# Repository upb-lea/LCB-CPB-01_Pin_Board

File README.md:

# Pin board LCB-CPB-01 for the LEA control board

This is the pin board extension board for the LEA control board LCB-CCB-01. Please refer to the [LCB-CCB-01 repository](https://github.com/upb-lea/LCB-CCB-01_LEA_Control_Board) for a PCB and project overview.

Note, that you also need to install the `LEA KiCad Library` to view this PCB in this repository. To do this, follow the instructions mentioned [here](https://github.com/upb-lea/LCB-CCB-01_LEA_Control_Board/blob/main/README.md#downloading-this-project-and-folder-structure).

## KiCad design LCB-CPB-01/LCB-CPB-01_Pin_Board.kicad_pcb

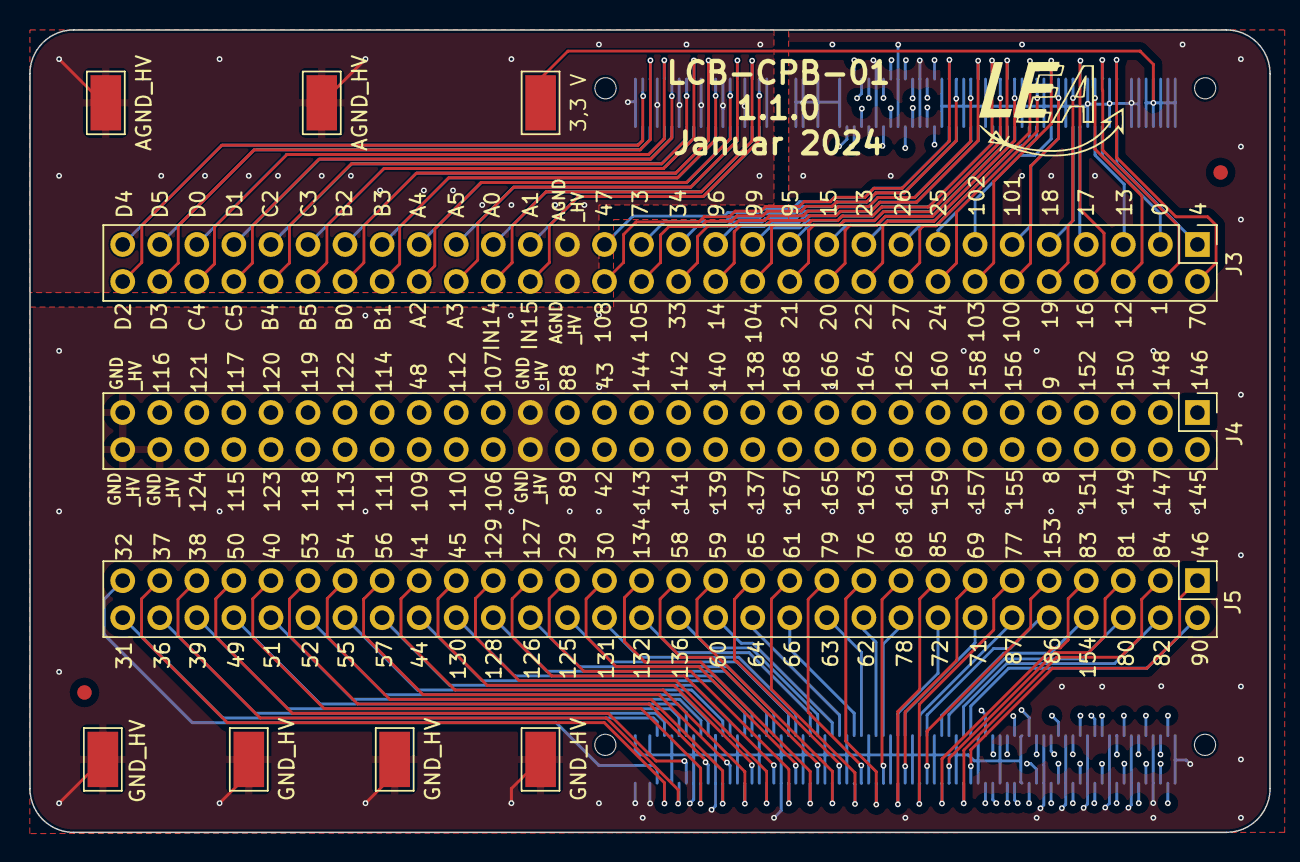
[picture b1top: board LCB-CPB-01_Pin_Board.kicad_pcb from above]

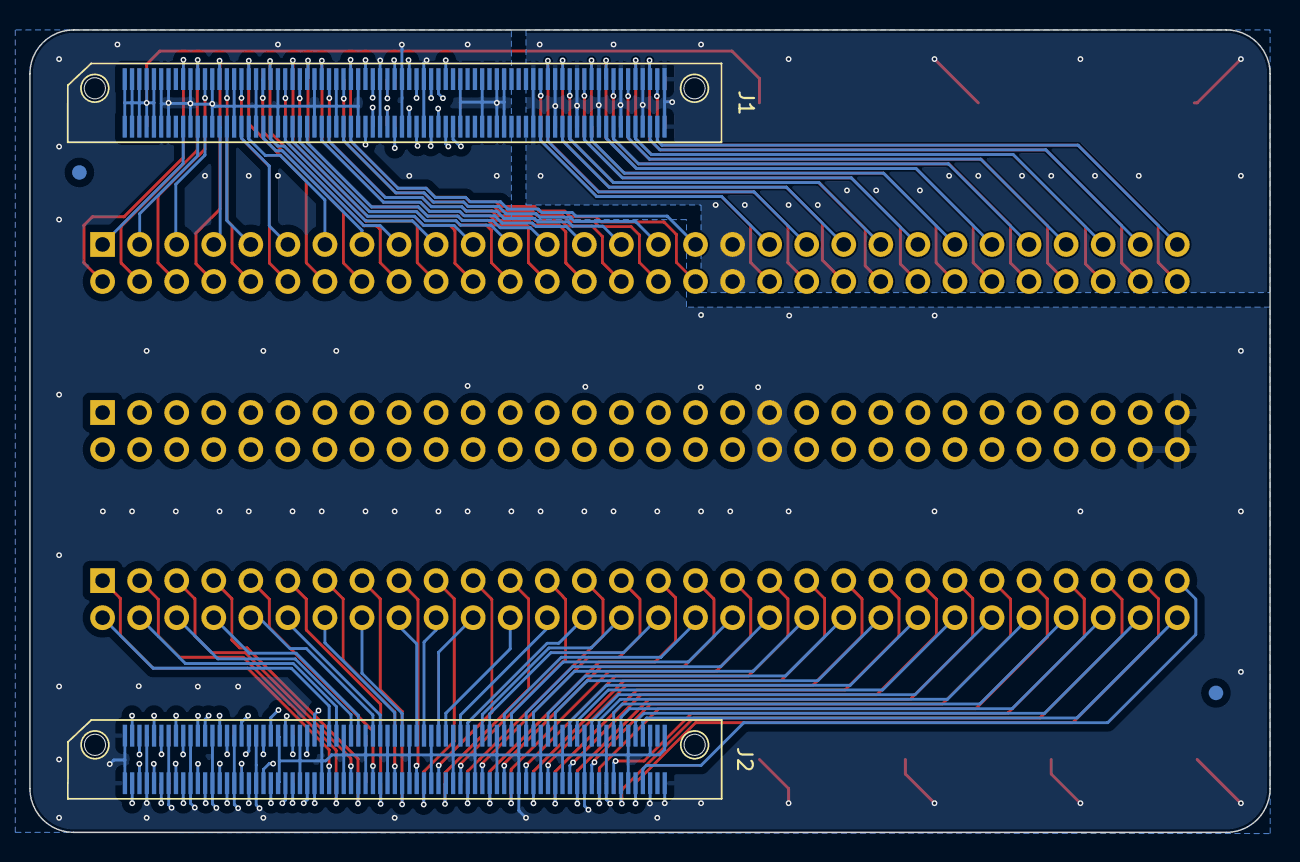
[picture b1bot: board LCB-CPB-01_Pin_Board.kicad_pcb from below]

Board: 4 copper layers, 85.0 x 55.0 mm, 17 parts (4 on the bottom side), 176 nets.

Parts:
3,3 V: TP_Keystone_Electronics_5019; TestPoint_KeystoneElectronics5019
AGND_HV: TP_Keystone_Electronics_5019; TestPoint_KeystoneElectronics5019
AGND_HV#2: TP_Keystone_Electronics_5019; TestPoint_KeystoneElectronics5019
GND_HV: TP_Keystone_Electronics_5019; TestPoint_KeystoneElectronics5019
GND_HV#2, GND_HV#3: TP_Keystone_Electronics_5019; TestPoint_KeystoneElectronics5019
J1, J2: ERM5-075-05.0-L-DV-K-TR; ERM5-075-05.0-L-DV
J3, J4, J5: 02x30_Row_Letter_Last; PinHeader_2x30_P2.54mm_Vertical
O1: SYM_LEA_Logo; SYM_lea_logo
O2, O3, O4, O5: Fiducial_medium; Fiducials_medium
TP7: TP_Keystone_Electronics_5019; TestPoint_KeystoneElectronics5019

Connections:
+3V3_Connector_HV: 3,3 V.1 (TP), J1.1, J1.2, J1.3, J1.4, J1.5, J1.6, J1.7, J1.8, J1.9, J1.10
ADC_A0_P: J1.118, J3.20a
ADC_A1_N: J1.116, J3.19a
ADC_A2_P: J1.123, J3.22b
ADC_A3_N: J1.121, J3.21b
ADC_A4_P: J1.124, J3.22a
ADC_A5_N: J1.122, J3.21a
ADC_B0_P: J1.129, J3.24b
ADC_B1_N: J1.127, J3.23b
ADC_B2_P: J1.130, J3.24a
ADC_B3_N: J1.128, J3.23a
ADC_B4_P: J1.135, J3.26b
ADC_B5_N: J1.133, J3.25b
ADC_C2_P: J1.136, J3.26a
ADC_C3_N: J1.134, J3.25a
ADC_C4_P: J1.141, J3.28b
ADC_C5_N: J1.139, J3.27b
ADC_D0_P: J1.142, J3.28a
ADC_D1_N: J1.140, J3.27a
ADC_D2_P: J1.147, J3.30b
ADC_D3_N: J1.145, J3.29b
ADC_D4_P: J1.148, J3.30a
ADC_D5_N: J1.146, J3.29a
ADC_IN14_P: J1.117, J3.20b
ADC_IN15_N: J1.115, J3.19b
AGND_HV: AGND_HV.1 (TP), AGND_HV#2.1 (TP), J1.113, J1.114, J1.119, J1.120, J1.125, J1.126, J1.131, J1.132, J1.137, J1.138, J1.143, J1.144, J1.149, J1.150, J3.18a, J3.18b
CANA_RX|GPIO36: J2.141, J5.29b
CANA_TX|GPIO37: J2.142, J5.29a
CANB_RX|GPIO39: J2.137, J5.28b
CANB_TX|GPIO38: J2.138, J5.28a
CM-I2CA_SCL|GPIO32: J2.144, J5.30a
CM-I2CA_SDA|GPIO31: J2.143, J5.30b
ENET_MDIO_CLK|GPIO105: J1.61, J3.16b
ENET_MDIO_DATA|GPIO106: J1.67, J4.20b
ENET_MII_COL|GPIO110: J1.69, J4.21b
ENET_MII_CRS|GPIO109: J1.73, J4.22b
ENET_MII_INTR|GPIO108: J1.63, J3.17b
ENET_MII_RX_CLK|GPIO111: J1.75, J4.23b
ENET_MII_RX_DV|GPIO112: J1.70, J4.21a
ENET_MII_RX_Data0|GPIO114: J1.76, J4.23a
ENET_MII_RX_Data1|GPIO115: J1.87, J4.27b
ENET_MII_RX_Data2|GPIO116: J1.92, J4.29a
ENET_MII_RX_Data3|GPIO117: J1.88, J4.27a
ENET_MII_RX_ERR|GPIO113: J1.79, J4.24b
ENET_MII_TX_CLK|GPIO120: J1.86, J4.26a
ENET_MII_TX_Data0|GPIO121: J1.90, J4.28a
ENET_MII_TX_Data1|GPIO122: J1.80, J4.24a
ENET_MII_TX_Data2|GPIO123: J1.85, J4.26b
ENET_MII_TX_Data3|GPIO124: J1.89, J4.28b
ENET_MII_TX_EN|GPIO118: J1.81, J4.25b
ENET_MII_TX_ERR|GPIO119: J1.82, J4.25a
ENET_PPS1|GPIO48: J1.74, J4.22a
ENET_PPSO|GPIO47: J1.64, J3.17a
ENET_REVMII_MDIO_RST|GPIO107: J1.68, J4.20a
ENET_RMII_CLK|GPIO73: J1.62, J3.16a
EPWM1A|GPIO145: J2.3, J4.1b
EPWM1B|GPIO146: J2.4, J4.1a
EPWM2A|GPIO147: J2.5, J4.2b
EPWM2B|GPIO148: J2.6, J4.2a
EPWM3A|GPIO149: J2.9, J4.3b
EPWM3B|GPIO150: J2.10, J4.3a
EPWM4A|GPIO151: J2.11, J4.4b
EPWM4B|GPIO152: J2.12, J4.4a
EPWM5A|GPIO8: J2.15, J4.5b
EPWM5B|GPIO9: J2.16, J4.5a
EPWM6A|GPIO155: J2.17, J4.6b
EPWM6B|GPIO156: J2.18, J4.6a
EPWM7A|GPIO157: J2.21, J4.7b
EPWM7B|GPIO158: J2.22, J4.7a
EPWM8A|GPIO159: J2.23, J4.8b
EPWM8B|GPIO160: J2.24, J4.8a
EPWM9A|GPIO161: J2.27, J4.9b
EPWM9B|GPIO162: J2.28, J4.9a
EPWM10A|GPIO163: J2.29, J4.10b
EPWM10B|GPIO164: J2.30, J4.10a
EPWM11A|GPIO165: J2.33, J4.11b
EPWM11B|GPIO166: J2.34, J4.11a
EPWM12A|GPIO167: J2.35, J4.12b
EPWM12B|GPIO168: J2.36, J4.12a
EPWM13A|GPIO137: J2.39, J4.13b
EPWM13B|GPIO138: J2.40, J4.13a
EPWM14A|GPIO139: J2.41, J4.14b
EPWM14B|GPIO140: J2.42, J4.14a
EPWM15A|GPIO141: J2.45, J4.15b
EPWM15B|GPIO142: J2.46, J4.15a
EPWM16A|GPIO143: J2.47, J4.16b
EPWM16B|GPIO144: J2.48, J4.16a
ESC_I2C_SCL|GPIO30: J2.106, J5.17a
ESC_I2C_SDA|GPIO29: J2.108, J5.18a
ESC_LATCH0|GPIO125: J2.107, J5.18b
ESC_LATCH1|GPIO126: J2.111, J5.19b
ESC_LED_ERR|GPIO60: J2.95, J5.14b
ESC_LED_LINK0_ACTIVE|GPIO58: J2.100, J5.15a
ESC_LED_LINK1_ACTIVE|GPIO59: J2.96, J5.14a
ESC_LED_RUN|GPIO61: J2.90, J5.12a
ESC_LED_STATE_RUN|GPIO62: J2.83, J5.10b
ESC_MDIO_CLK|GPIO46: J2.58, J5.1a
ESC_MDIO_DATA|GPIO153: J2.70, J5.5a
ESC_PHY0_LINKSTATUS|GPIO86: J2.69, J5.5b
ESC_PHY1_LINKSTATUS|GPIO68: J2.82, J5.9a
ESC_PHY_CLK|GPIO154: J2.65, J5.4b
ESC_PHY_RESETn|GPIO76: J2.84, J5.10a
ESC_RX0_CLK|GPIO77: J2.72, J5.6a
ESC_RX0_DATA0|GPIO80: J2.63, J5.3b
ESC_RX0_DATA1|GPIO81: J2.64, J5.3a
ESC_RX0_DATA2|GPIO82: J2.59, J5.2b
ESC_RX0_DATA3|GPIO83: J2.66, J5.4a
ESC_RX0_DV|GPIO78: J2.81, J5.9b
ESC_RX0_ERR|GPIO79: J2.88, J5.11a
ESC_RX1_CLK|GPIO69: J2.76, J5.7a
ESC_RX1_DATA0|GPIO63: J2.87, J5.11b
ESC_RX1_DATA1|GPIO64: J2.93, J5.13b
ESC_RX1_DATA2|GPIO65: J2.94, J5.13a
ESC_RX1_DATA3|GPIO66: J2.89, J5.12b
ESC_RX1_DV|GPIO136: J2.99, J5.15b
ESC_RX1_ERR|GPIO71: J2.75, J5.7b
ESC_SYNC0|GPIO127: J2.112, J5.19a
ESC_SYNC1|GPIO128: J2.113, J5.20b
ESC_TX0_CLK|GPIO85: J2.78, J5.8a
ESC_TX0_DATA0|GPIO87: J2.71, J5.6b
ESC_TX0_DATA1|GPIO88: J2.54, J4.18a
ESC_TX0_DATA2|GPIO89: J2.53, J4.18b
ESC_TX0_DATA3|GPIO90: J2.57, J5.1b
ESC_TX0_ENA|GPIO84: J2.60, J5.2a
ESC_TX1_CLK|GPIO130: J2.117, J5.21b
ESC_TX1_DATA0|GPIO131: J2.105, J5.17b
ESC_TX1_DATA1|GPIO132: J2.101, J5.16b
ESC_TX1_DATA2|GPIO134: J2.102, J5.16a
ESC_TX1_DATA3|GPIO72: J2.77, J5.8b
ESC_TX1_ENA|GPIO129: J2.114, J5.20a
GND_HV: GND_HV.1 (TP), GND_HV#2.1 (TP), GND_HV#3.1 (TP), J1.11, J1.12, J1.13, J1.14, J1.19, J1.20, J1.25, J1.26, J1.31, J1.32, J1.37, J1.38, J1.43, J1.44, J1.53, J1.54, J1.59, J1.60, J1.65, J1.66, J1.71, J1.72, J1.77, J1.78, J1.83, J1.84, J1.93, J1.94, J1.99, J1.100, J1.103, J1.104, J1.105, J1.106, J2.1, J2.2, J2.7, J2.8, J2.13, J2.14, J2.19, J2.20, J2.25, J2.26, J2.31, J2.32, J2.37, J2.38, J2.43, J2.44, J2.49, J2.50, J2.55, J2.56, J2.61, J2.62, J2.67, J2.68, J2.73, J2.74, J2.79, J2.80, J2.85, J2.86, J2.91, J2.92, J2.97, J2.98, J2.103, J2.104, J2.109, J2.110, J2.115, J2.116, J2.121, J2.122, J2.127, J2.128, J2.133, J2.134, J2.139, J2.140, J2.145, J2.146, J2.149, J2.150, J4.19a, J4.19b, J4.29b, J4.30a, J4.30b, TP7.1 (TP)
GPIO14_nErr4: J1.55, J3.14b
GPIO15_Err1: J1.48, J3.11a
GPIO20_nErr1: J1.47, J3.11b
GPIO21_nErr2: J1.49, J3.12b
GPIO33: J1.57, J3.15b
GPIO34: J1.58, J3.15a
GPIO40: J2.132, J5.26a
GPIO41: J2.120, J5.22a
GPIO44: J2.119, J5.22b
GPIO45: J2.118, J5.21a
GPIO49: J2.135, J5.27b
GPIO50: J2.136, J5.27a
GPIO51: J2.131, J5.26b
GPIO52: J2.129, J5.25b
GPIO53: J2.130, J5.25a
GPIO95_Err2: J1.50, J3.12a
GPIO96_Err4: J1.56, J3.14a
GPIO99_Err3: J1.52, J3.13a
GPIO104_nErr3: J1.51, J3.13b
I2CA_SCL|GPIO1: J1.21, J3.2b
I2CA_SDA|GPIO0: J1.22, J3.2a
MCAN_RX|GPIO70: J1.17, J3.1b
MCAN_TX|GPIO4: J1.18, J3.1a
SCIB_RX|GPIO23: J1.46, J3.10a
SCIB_TX|GPIO22: J1.45, J3.10b
SCIC_RX|GPIO13: J1.24, J3.3a
SCIC_TX|GPIO12: J1.23, J3.3b
SPIA_CLK|GPIO18: J1.30, J3.5a
SPIA_MISO|GPIO17: J1.28, J3.4a
SPIA_MOSI|GPIO16: J1.27, J3.4b
SPIA_STEn|GPIO19: J1.29, J3.5b
SPIB_CLK|GPIO26: J1.42, J3.9a
SPIB_MISO|GPIO25: J1.40, J3.8a
SPIB_MOSI|GPIO24: J1.39, J3.8b
SPIB_STEn|GPIO27: J1.41, J3.9b
SPIC_CLK|GPIO102: J1.36, J3.7a
SPIC_MISO|GPIO101: J1.34, J3.6a
SPIC_MOSI|GPIO100: J1.33, J3.6b
SPIC_STEn|GPIO103: J1.35, J3.7b
SSIA_CLK|GPIO56: J2.124, J5.23a
SSIA_FSS|GPIO57: J2.123, J5.23b
SSIA_RX|GPIO55: J2.125, J5.24b
SSIA_TX|GPIO54: J2.126, J5.24a
UARTA_RX|GPIO43: J2.52, J4.17a
UARTA_TX|GPIO42: J2.51, J4.17b

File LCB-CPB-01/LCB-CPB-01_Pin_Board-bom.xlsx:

Prj: | LCB-CPB-01: Pin_Borad |  |  |  |  | Board Qty: | 100
Co.: | PADERBORN UNIVERSITY DEPARTMENT OF POWER ELECTRONICS AND ELECTRICAL DRIVES |  |  |  |  | Unit Cost: | 21.793
Prj date: | Mi 20 Dez 2023 11:09:16 CET |  |  |  |  | Total Cost: | 2179.3 |  |  |  |  | 2179.3 | 3 of 3 parts found
$ date: | 2023-12-20 11:20:31
Global Part Info |  |  |  |  |  |  |  | Mouser
Refs | Value | Footprint | Manf | Manf# | Qty | Unit$ | Ext$ | Avail | Purch | Unit$ | MOQ | Ext$ | Cat#
J1,J2 | ERM5-075-05.0-L-DV-K-TR | ERM5-075-05.0-L-DV | Samtec | ERM5-075-05.0-L-DV-K-TR | 200 | 7.66 | 1532.0 | 184 |  | 7.66 | 1 | 1532.0 | 200-ERM5075050LDVKTR
J3-J5 | 02x30_Row_Letter_Last | PinHeader_2x30_P2.54mm_Vertical | Amphenol | 77313-118-60LF | 300 | 1.74 | 522.0 | 192 |  | 1.74 | 1 | 522.0 | 649-77313-118-60LF
TP1-TP7 | TP_Keystone_Electronics_5019 | TestPoint_KeystoneElectronics5019 | Keystone Electronics | 5019 | 700 | 0.179 | 125.3 | 231183 |  | 0.179 | 1 | 125.3 | 534-5019
 |  |  |  |  |  | Total Purchase: | 0 | Buy here |  |  |  | 0
KiCost® v1.1.18 |  |  |  |  |  | Purchase description:
 |  |  |  |  |  |  |  |  | 0
 |  |  |  |  |  |  |  |  | 0

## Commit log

2023-12-13 add readme and .gitignore
2023-12-13 Inital commit Pin_Borad
2023-12-13 First Review
2023-12-14 2nd Review
2023-12-14 2nd Review shift 3,3V Connection
2023-12-14 fix filepath for symbol and footprint library
2023-12-15 2nd Review Footprint update
2023-12-17 Change comment in scematic
2023-12-18 Update Silkscreen
2023-12-19 Separate GND into AGND_HV and GND_HV (+Silkscreen)
2023-12-20 change probe connectors, fix warnings in schematic
2023-12-20 add pdf schematic and bom
2024-01-17 Changed Positions of conectors
    In the layout the conectors J1 and J2 had to be chaged.
2024-01-19 add changelog
2024-01-23 Routing for changed positions of connectors
2024-01-24 bump schematic version to 1.1.0
2024-01-24 bump version to 1.1.0
2024-02-05 fix typing error CPD -> CPB
